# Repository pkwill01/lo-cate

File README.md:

# lo-cate
A PCB and firmware project to create a simple LoRa capable device with an intergrated IMU. 

## Firmware

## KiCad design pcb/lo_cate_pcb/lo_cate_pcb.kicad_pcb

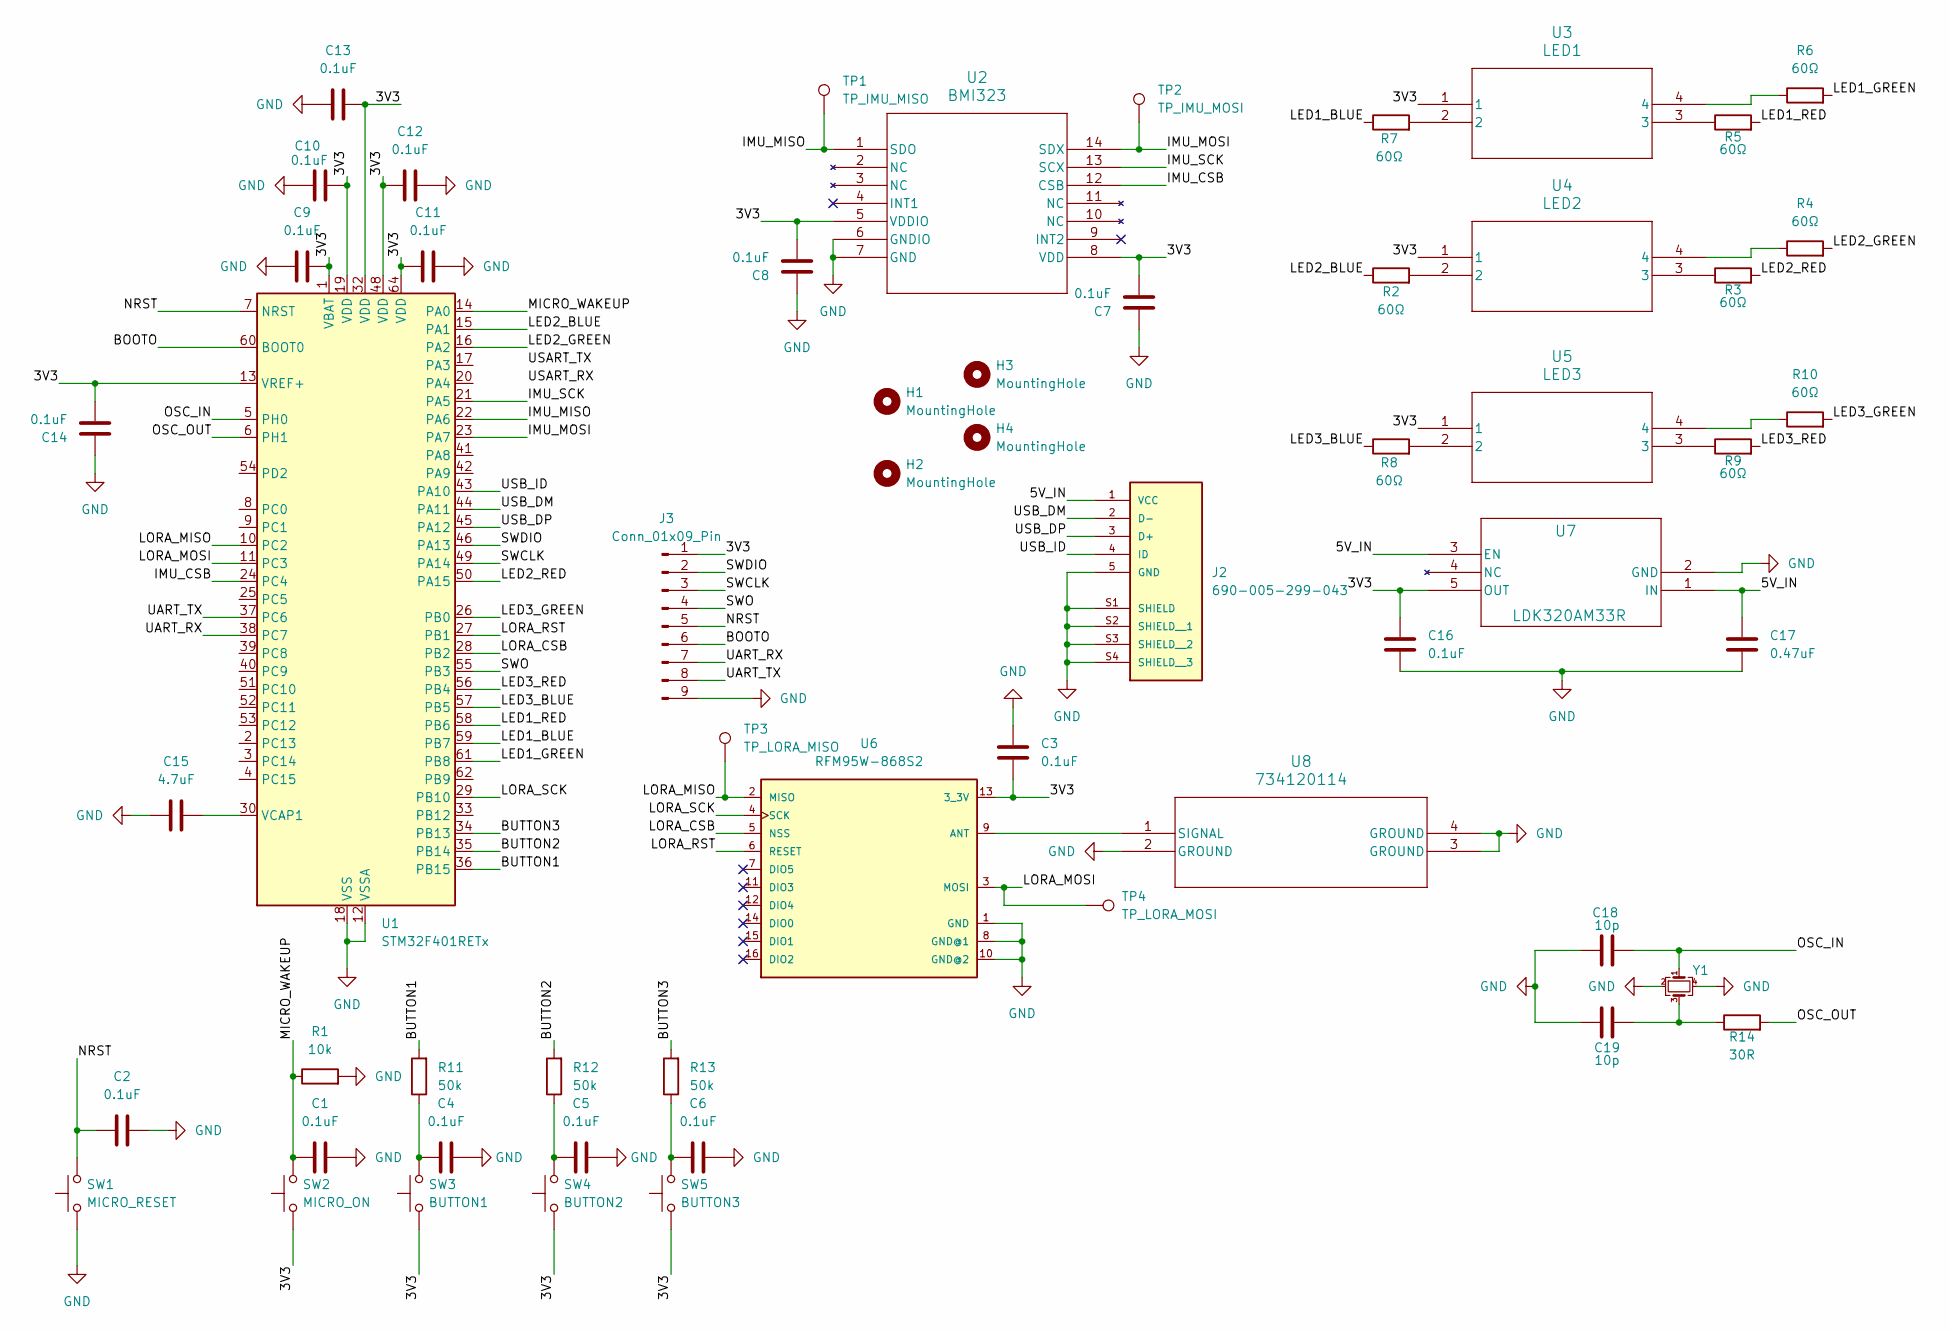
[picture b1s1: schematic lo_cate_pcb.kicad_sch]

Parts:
C1, C2, C3, C4, C5, C6, C7, C8, C9, C10, C11, C12, C13, C14, C16: 0.1uF; C_0805_2012Metric_Pad1.18x1.45mm_HandSolder
C15: 4.7uF; C_0805_2012Metric_Pad1.18x1.45mm_HandSolder
C17: 0.47uF; C_0805_2012Metric_Pad1.18x1.45mm_HandSolder
C18, C19: 10p; C_0805_2012Metric_Pad1.18x1.45mm_HandSolder
H1, H2, H3, H4: MountingHole; MountingHole_3.2mm_M3
J2: 690-005-299-043; EDAC_690-005-299-043; PARTREV 11
J3: Conn_01x09_Pin; PinSocket_1x09_P1.27mm_Vertical
R1: 10k; R_0805_2012Metric_Pad1.20x1.40mm_HandSolder
R2, R3, R4, R5, R6, R7, R8, R9, R10: 60Ω; R_0805_2012Metric_Pad1.20x1.40mm_HandSolder
R11, R12, R13: 50k; R_0805_2012Metric_Pad1.20x1.40mm_HandSolder
R14: 30R; R_0805_2012Metric_Pad1.20x1.40mm_HandSolder
SW1: MICRO_RESET; SW_SPST_PTS647_Sx38
SW2: MICRO_ON; SW_SPST_PTS647_Sx38
SW3: BUTTON1; SW_SPST_PTS647_Sx38
SW4: BUTTON2; SW_SPST_PTS647_Sx38
SW5: BUTTON3; SW_SPST_PTS647_Sx38
TP1: TP_IMU_MISO; TestPoint_Pad_D2.0mm
TP2: TP_IMU_MOSI; TestPoint_Pad_D2.0mm
TP3: TP_LORA_MISO; TestPoint_Pad_D2.0mm
TP4: TP_LORA_MOSI; TestPoint_Pad_D2.0mm
U1: STM32F401RETx; LQFP-64_10x10mm_P0.5mm
U2: BMI323; BMI323_BOS-M
U3: LED1; 150141M173100_WRE-M
U4: LED2; 150141M173100_WRE-M
U5: LED3; 150141M173100_WRE-M
U6: RFM95W-868S2; XCVR_RFM95W-868S2
U7: LDK320AM33R; SOT23-5L_STM-M
U8: 734120114; 73412-0114_MOL
Y1: Crystal_GND24_Small; Crystal_SMD_7050-4Pin_7.0x5.0mm

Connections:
/3V3: C3.2, C7.2, C8.2, C9.1, C10.1, C11.2, C12.2, C13.2, C14.2, C16.1, J3.1, SW2.1, SW3.1, SW4.1, SW5.1, U1.1 (VBAT), U1.13 (VREF+), U1.19 (VDD), U1.32 (VDD), U1.48 (VDD), U1.64 (VDD), U2.5 (VDDIO), U2.8 (VDD), U3.1, U4.1, U5.1, U6.13 (3_3V), U7.5 (OUT)
/5V_IN: C17.1, J2.1 (VCC), U7.1 (IN), U7.3 (EN)
/BOOTO: J3.6, U1.60 (BOOT0)
/BUTTON1: R11.2, U1.36 (PB15)
/BUTTON2: R12.2, U1.35 (PB14)
/BUTTON3: R13.2, U1.34 (PB13)
/IMU_CSB: U1.24 (PC4), U2.12 (CSB)
/IMU_MISO: TP1.1, U1.22 (PA6), U2.1 (SDO)
/IMU_MOSI: TP2.1, U1.23 (PA7), U2.14 (SDX)
/IMU_SCK: U1.21 (PA5), U2.13 (SCX)
/LED1_BLUE: R7.1, U1.59 (PB7)
/LED1_GREEN: R6.2, U1.61 (PB8)
/LED1_RED: R5.2, U1.58 (PB6)
/LED2_BLUE: R2.1, U1.15 (PA1)
/LED2_GREEN: R4.2, U1.16 (PA2)
/LED2_RED: R3.2, U1.50 (PA15)
/LED3_BLUE: R8.1, U1.57 (PB5)
/LED3_GREEN: R10.2, U1.26 (PB0)
/LED3_RED: R9.2, U1.56 (PB4)
/LORA_CSB: U1.28 (PB2), U6.5 (NSS)
/LORA_MISO: TP3.1, U1.10 (PC2), U6.2 (MISO)
/LORA_MOSI: TP4.1, U1.11 (PC3), U6.3 (MOSI)
/LORA_RST: U1.27 (PB1), U6.6 (RESET)
/LORA_SCK: U1.29 (PB10), U6.4 (SCK)
/MICRO_WAKEUP: C1.2, R1.1, SW2.2, U1.14 (PA0)
/NRST: C2.2, J3.5, SW1.2, U1.7 (NRST)
/OSC_IN: C18.1, U1.5 (PH0), Y1.1
/OSC_OUT: R14.2, U1.6 (PH1)
/SWCLK: J3.3, U1.49 (PA14)
/SWDIO: J3.2, U1.46 (PA13)
/SWO: J3.4, U1.55 (PB3)
/UART_RX: J3.7, U1.38 (PC7)
/UART_TX: J3.8, U1.37 (PC6)
/USB_DM: J2.2 (D-), U1.44 (PA11)
/USB_DP: J2.3 (D+), U1.45 (PA12)
/USB_ID: J2.4 (ID), U1.43 (PA10)
GND: C1.1, C2.1, C3.1, C4.1, C5.1, C6.1, C7.1, C8.1, C9.2, C10.2, C11.1, C12.1, C13.1, C14.1, C15.2, C16.2, C17.2, C18.2, C19.2, J2.5 (GND), J2.S1 (SHIELD), J2.S2 (SHIELD__1), J2.S3 (SHIELD__2), J2.S4 (SHIELD__3), J3.9, R1.2, SW1.1, U1.12 (VSSA), U1.18 (VSS), U1.31 (VSS), U1.47 (VSS), U1.63 (VSS), U2.6 (GNDIO), U2.7 (GND), U6.1 (GND), U6.8 (GND@1), U6.10 (GND@2), U7.2 (GND), U8.2 (GROUND), U8.3 (GROUND), U8.4 (GROUND), Y1.2, Y1.4
unnamed: C4.2, R11.1, SW3.2
unnamed: C5.2, R12.1, SW4.2
unnamed: C6.2, R13.1, SW5.2
unnamed: C19.1, R14.1, Y1.3
unnamed: R2.2, U4.2
unnamed: R3.1, U4.3
unnamed: R4.1, U4.4
unnamed: R5.1, U3.3
unnamed: R6.1, U3.4
unnamed: R7.2, U3.2
unnamed: R8.2, U5.2
unnamed: R9.1, U5.3
unnamed: R10.1, U5.4
unnamed: C15.1, U1.30 (VCAP1)
unnamed: U6.9 (ANT), U8.1 (SIGNAL)

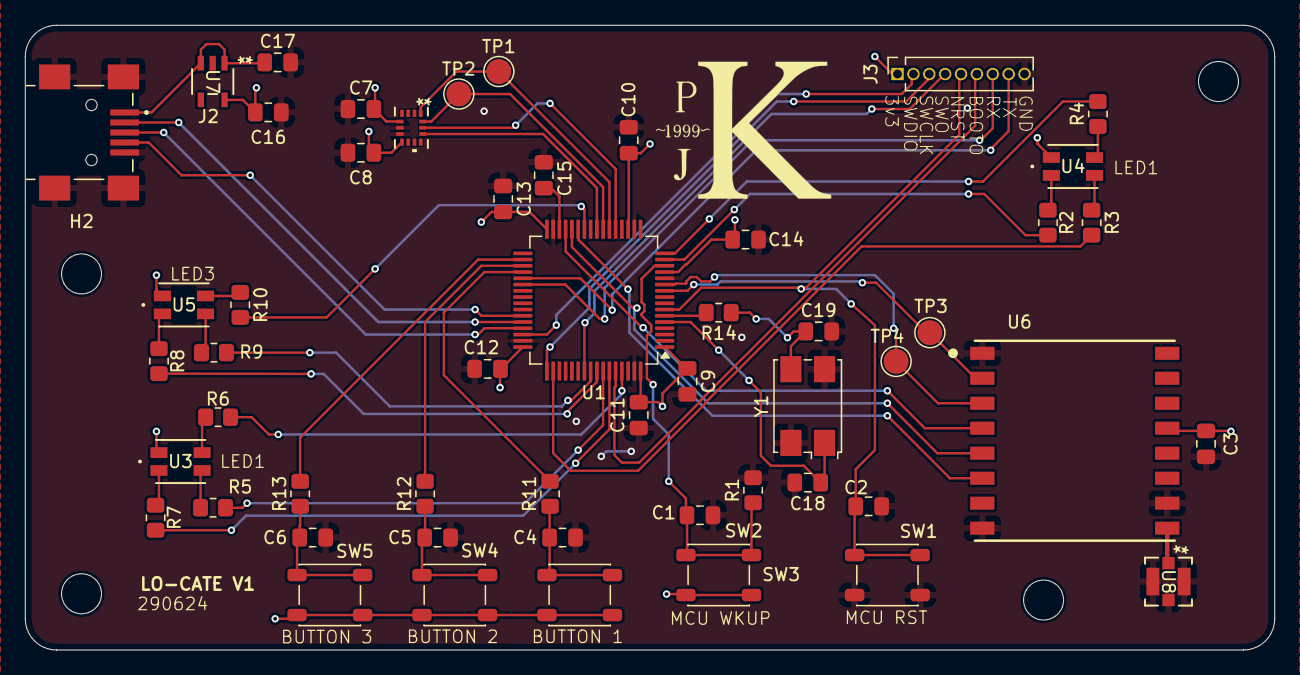
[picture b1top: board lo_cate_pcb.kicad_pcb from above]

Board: 4 copper layers, 100.0 x 50.0 mm, 57 parts (0 on the bottom side), 52 nets.

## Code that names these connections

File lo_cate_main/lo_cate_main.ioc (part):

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Mcu.Name=STM32F401R(D-E)Tx
Mcu.Package=LQFP64
Mcu.UserName=STM32F401RETx
PA1.GPIOParameters=GPIO_Label
PA1.GPIO_Label=LED2_BLUE
PA1.Signal=S_TIM2_CH2
PA11.GPIOParameters=GPIO_Label
PA11.GPIO_Label=USB_DM
PA11.Mode=Device_Only
PA11.Signal=USB_OTG_FS_DM
PA12.GPIOParameters=GPIO_Label
PA12.GPIO_Label=USB_DP
PA12.Mode=Device_Only
PA12.Signal=USB_OTG_FS_DP
PA13.Mode=Trace_Asynchronous_SW
PA13.Signal=SYS_JTMS-SWDIO
PA14.Mode=Trace_Asynchronous_SW
PA14.Signal=SYS_JTCK-SWCLK
PA15.GPIOParameters=GPIO_Label
PA15.GPIO_Label=LED2_RED
PA15.Signal=S_TIM2_CH1_ETR
PA2.GPIOParameters=GPIO_Label
PA2.GPIO_Label=LED2_GREEN
PA2.Signal=S_TIM2_CH3
PA5.GPIOParameters=GPIO_Label
PA5.GPIO_Label=IMU_INT1
PA5.Signal=GPIO_Input
PA6.GPIOParameters=GPIO_Label
PA6.GPIO_Label=IMU_INT2
PA6.Signal=GPIO_Input
PA8.GPIOParameters=GPIO_Label
PA8.GPIO_Label=IMU_SCL
PA8.Mode=I2C
PA8.Signal=I2C3_SCL
PA9.GPIOParameters=GPIO_Label
PA9.GPIO_Label=IMU_SA0
PA9.Signal=GPIO_Output
PB0.GPIOParameters=GPIO_Label
PB0.GPIO_Label=LED3_GREEN
PB0.Signal=S_TIM3_CH3
PB1.GPIOParameters=PinState,GPIO_Label
PB1.GPIO_Label=LORA_RST
PB1.PinState=GPIO_PIN_RESET
PB1.Signal=GPIO_Output
PB10.GPIOParameters=GPIO_Label
PB10.GPIO_Label=LORA_SCK
PB10.Mode=Full_Duplex_Master
PB10.Signal=SPI2_SCK
PB13.GPIOParameters=GPIO_Label
PB13.GPIO_Label=BUTTON3
PB13.Signal=GPIO_Input
PB14.GPIOParameters=GPIO_Label
PB14.GPIO_Label=BUTTON2
PB14.Signal=GPIO_Input
PB15.GPIOParameters=GPIO_Label
PB15.GPIO_Label=BUTTON1
PB15.Signal=GPIO_Input
PB2.GPIOParameters=PinState,GPIO_Label
PB2.GPIO_Label=LORA_CSB
PB2.PinState=GPIO_PIN_RESET
PB2.Signal=GPIO_Output
PB3.Mode=Trace_Asynchronous_SW
PB3.Signal=SYS_JTDO-SWO
PB4.GPIOParameters=GPIO_Label
PB4.GPIO_Label=LED3_RED
PB4.Signal=S_TIM3_CH1
PB5.GPIOParameters=GPIO_Label
PB5.GPIO_Label=LED3_BLUE
PB5.Signal=S_TIM3_CH2
PB6.GPIOParameters=GPIO_Label
PB6.GPIO_Label=LED1_RED
PB6.Signal=S_TIM4_CH1
PB7.GPIOParameters=GPIO_Label
PB7.GPIO_Label=LED1_BLUE
PB7.Signal=S_TIM4_CH2
PB8.GPIOParameters=GPIO_Label
PB8.GPIO_Label=LED1_GREEN
PB8.Signal=S_TIM4_CH3
PC10.GPIOParameters=GPIO_Label
PC10.GPIO_Label=LORA_DIO0
PC10.Signal=GPIO_Input
PC11.GPIOParameters=GPIO_Label
PC11.GPIO_Label=LORA_DIO1
PC11.Signal=GPIO_Input
PC12.GPIOParameters=GPIO_Label
PC12.GPIO_Label=LORA_DIO2
PC12.Signal=GPIO_Input
PC2.GPIOParameters=GPIO_Label
PC2.GPIO_Label=LORA_MISO
PC2.Mode=Full_Duplex_Master
PC2.Signal=SPI2_MISO
PC3.GPIOParameters=GPIO_Label
PC3.GPIO_Label=LORA_MOSI
PC3.Mode=Full_Duplex_Master
PC3.Signal=SPI2_MOSI
PC6.Mode=Asynchronous
PC6.Signal=USART6_TX
PC7.Mode=Asynchronous
PC7.Signal=USART6_RX
PC9.GPIOParameters=GPIO_Label
PC9.GPIO_Label=IMU_SDA
PC9.Mode=I2C
PC9.Signal=I2C3_SDA
PH0\ -\ OSC_IN.Mode=HSE-External-Oscillator
PH0\ -\ OSC_IN.Signal=RCC_OSC_IN
PH1\ -\ OSC_OUT.Mode=HSE-External-Oscillator
PH1\ -\ OSC_OUT.Signal=RCC_OSC_OUT
RCC.HSE_VALUE=8000000
RCC.SYSCLKFreq_VALUE=72000000
RCC.SYSCLKSource=RCC_SYSCLKSOURCE_PLLCLK
board=custom

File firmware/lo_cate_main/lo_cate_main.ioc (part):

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Mcu.Name=STM32F401R(D-E)Tx
Mcu.Package=LQFP64
Mcu.UserName=STM32F401RETx
PA1.GPIOParameters=PinState
PA1.PinState=GPIO_PIN_SET
PA1.Signal=GPIO_Output
PA10.Mode=OTG/Dual_Role_Device
PA10.Signal=USB_OTG_FS_ID
PA11.GPIOParameters=GPIO_Label
PA11.GPIO_Label=USB_DM
PA11.Mode=OTG/Dual_Role_Device
PA11.Signal=USB_OTG_FS_DM
PA12.GPIOParameters=GPIO_Label
PA12.GPIO_Label=USB_DP
PA12.Mode=OTG/Dual_Role_Device
PA12.Signal=USB_OTG_FS_DP
PA13.Mode=Trace_Asynchronous_SW
PA13.Signal=SYS_JTMS-SWDIO
PA14.Mode=Trace_Asynchronous_SW
PA14.Signal=SYS_JTCK-SWCLK
PA15.GPIOParameters=GPIO_Label
PA15.GPIO_Label=LED2_RED
PA15.Signal=S_TIM2_CH1_ETR
PA2.GPIOParameters=GPIO_Label
PA2.GPIO_Label=LED2_GREEN
PA2.Signal=S_TIM2_CH3
PA5.GPIOParameters=GPIO_Label
PA5.GPIO_Label=IMU_SCK
PA5.Mode=Full_Duplex_Master
PA5.Signal=SPI1_SCK
PA6.GPIOParameters=GPIO_Label
PA6.GPIO_Label=IMU_MISO
PA6.Mode=Full_Duplex_Master
PA6.Signal=SPI1_MISO
PA7.GPIOParameters=GPIO_Label
PA7.GPIO_Label=IMU_MOSI
PA7.Mode=Full_Duplex_Master
PA7.Signal=SPI1_MOSI
PB0.GPIOParameters=GPIO_Label
PB0.GPIO_Label=LED3_GREEN
PB0.Signal=S_TIM3_CH3
PB1.GPIOParameters=PinState,GPIO_Label
PB1.GPIO_Label=LORA_RST
PB1.PinState=GPIO_PIN_SET
PB1.Signal=GPIO_Output
PB13.GPIOParameters=GPIO_Label
PB13.GPIO_Label=LORA_SCK
PB13.Mode=Full_Duplex_Master
PB13.Signal=SPI2_SCK
PB2.GPIOParameters=PinState,GPIO_Label
PB2.GPIO_Label=LORA_CSB
PB2.PinState=GPIO_PIN_SET
PB2.Signal=GPIO_Output
PB3.Mode=Trace_Asynchronous_SW
PB3.Signal=SYS_JTDO-SWO
PB4.GPIOParameters=GPIO_Label
PB4.GPIO_Label=LED3_RED
PB4.Signal=S_TIM3_CH1
PB5.GPIOParameters=PinState
PB5.PinState=GPIO_PIN_SET
PB5.Signal=GPIO_Output
PB6.GPIOParameters=GPIO_Label
PB6.GPIO_Label=LED1_RED
PB6.Signal=S_TIM4_CH1
PB7.GPIOParameters=PinState
PB7.PinState=GPIO_PIN_SET
PB7.Signal=GPIO_Output
PB8.GPIOParameters=GPIO_Label
PB8.GPIO_Label=LED1_GREEN
PB8.Signal=S_TIM4_CH3
PC2.GPIOParameters=GPIO_Label
PC2.GPIO_Label=LORA_MISO
PC2.Mode=Full_Duplex_Master
PC2.Signal=SPI2_MISO
PC3.GPIOParameters=GPIO_Label
PC3.GPIO_Label=LORA_MOSI
PC3.Mode=Full_Duplex_Master
PC3.Signal=SPI2_MOSI
PC4.GPIOParameters=PinState,GPIO_Label
PC4.GPIO_Label=IMU_CSB
PC4.PinState=GPIO_PIN_RESET
PC4.Signal=GPIO_Output
PC6.Mode=Asynchronous
PC6.Signal=USART6_TX
PC7.Mode=Asynchronous
PC7.Signal=USART6_RX
PH0\ -\ OSC_IN.Mode=HSE-External-Oscillator
PH0\ -\ OSC_IN.Signal=RCC_OSC_IN
PH1\ -\ OSC_OUT.Mode=HSE-External-Oscillator
PH1\ -\ OSC_OUT.Signal=RCC_OSC_OUT
RCC.HSE_VALUE=8000000
RCC.SYSCLKFreq_VALUE=16000000
board=custom

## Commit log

2024-06-20 Basic PCB Design
2024-06-21 Found footprint and sch files for most components
2024-06-21 Added footprint files for most componenets
2024-06-22 Added basic firmware folder
2024-06-22 Finished basic PCB connections, now need to do the power electronics and antenna
2024-06-23 USB connector added to pcb, All that is left is power electronics and antenna
2024-06-23 Started the PCB Layout
2024-06-24 Added smt connector
2024-06-26 Most PCB Routing is complete
2024-06-27 Final PCB design done
2024-06-29 Changed PCB to a 4 Layer Version
2024-06-29 Added an external crystal oscillator
2024-06-29 Finished PCB?
2024-06-29 Moved the Oscillator slightly to help with assembly
2024-06-29 Altered the Oscillator Path
2024-06-29 broke a usart to header pins
2024-06-29 Submitted PCB for manufactoring
2024-07-05 Added the step files for all the componenets on the PCB
2024-07-05 Updated the readme
2024-07-05 Updated readme to reflect finished PCB design
2024-07-06 Added some additional PCB to do's
2024-07-09 Changes to readme and got the led working
2024-07-09 zip commit
2024-07-10 minor code changes
2024-07-13 Reading form the LORA module is now working
2024-07-14 Basic lora template driver written
2024-07-20 Put the electronics into its own repo lo-cate-pcb
2024-07-23 Updated the ioc file for pcb v2
